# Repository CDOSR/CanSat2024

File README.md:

# CanSat2024

Welcome to the CanSat2024 project repository. This project is dedicated to the design, development, and deployment of a CanSat, a small satellite designed for educational purposes.

## Table of Contents
- [Introduction](#introduction)
- [Project Structure](#project-structure)
- [Getting Started](#getting-started)
- [Hardware](#hardware)
- [Software](#software)
- [Contributing](#contributing)
- [License](#license)

## Introduction
CanSat2024 is an educational initiative aimed at providing hands-on experience in satellite engineering. Participants will design, build, and launch a small satellite to achieve specific mission objectives.

## Project Structure
- `Documents/`: Documentation and guidelines for the project.
- `Hardware/`: Schematics, PCB designs, and hardware-related files.
- `Software/`: Source code for the CanSat's firmware and ground control software.

## Getting Started
### Prerequisites
- Basic understanding of electronics and programming.
- Required tools and components listed in `docs/tools_and_components.md`.

### Installation
1. Clone the repository:
    ```sh
    git clone https://github.com/CDOSR/CanSat2024.git
    ```
2. Navigate to the project directory:
    ```sh
    cd CanSat2024
    ```

## Hardware
Details about the hardware components, including sensors, microcontrollers, and power systems, can be found in the `hardware/` directory. Refer to `hardware/README.md` for more information.

## Software
The software for the CanSat includes firmware for onboard systems and software for ground control. Instructions for building and deploying the software are available in the `software/` directory. Refer to `software/README.md` for more details.

## Contributing
We welcome contributions from the community. Please read `CONTRIBUTING.md` for guidelines on how to contribute to the project.

## License
This project is licensed under the MIT License. See the `LICENSE` file for details.

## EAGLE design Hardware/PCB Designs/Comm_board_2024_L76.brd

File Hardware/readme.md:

# Hardware

CAD sources for the custom PCBs designed for CanSat 2024.

## Contents

- `PCB Designs/` — Eagle `.sch` (schematic) and `.brd` (board layout) files
  for the four custom boards:
  - `Comm_board_2024_L76` — communications board with Quectel L76 GNSS
  - `Comm_board_2024_M8N` — communications board with u-blox NEO-M8N GNSS
  - `Power_board_2024` — power distribution and battery management
  - `Sensor_board_2024` — sensor aggregation (IMU, environmental, etc.)

## Component datasheets

Datasheets for the third-party components used on these boards live under
[`Documentation/Hardware/Data Sheets/`](../Documentation/Hardware/Data%20Sheets/)
— kept separate so this tree stays focused on our own CAD sources rather
than vendor reference material.

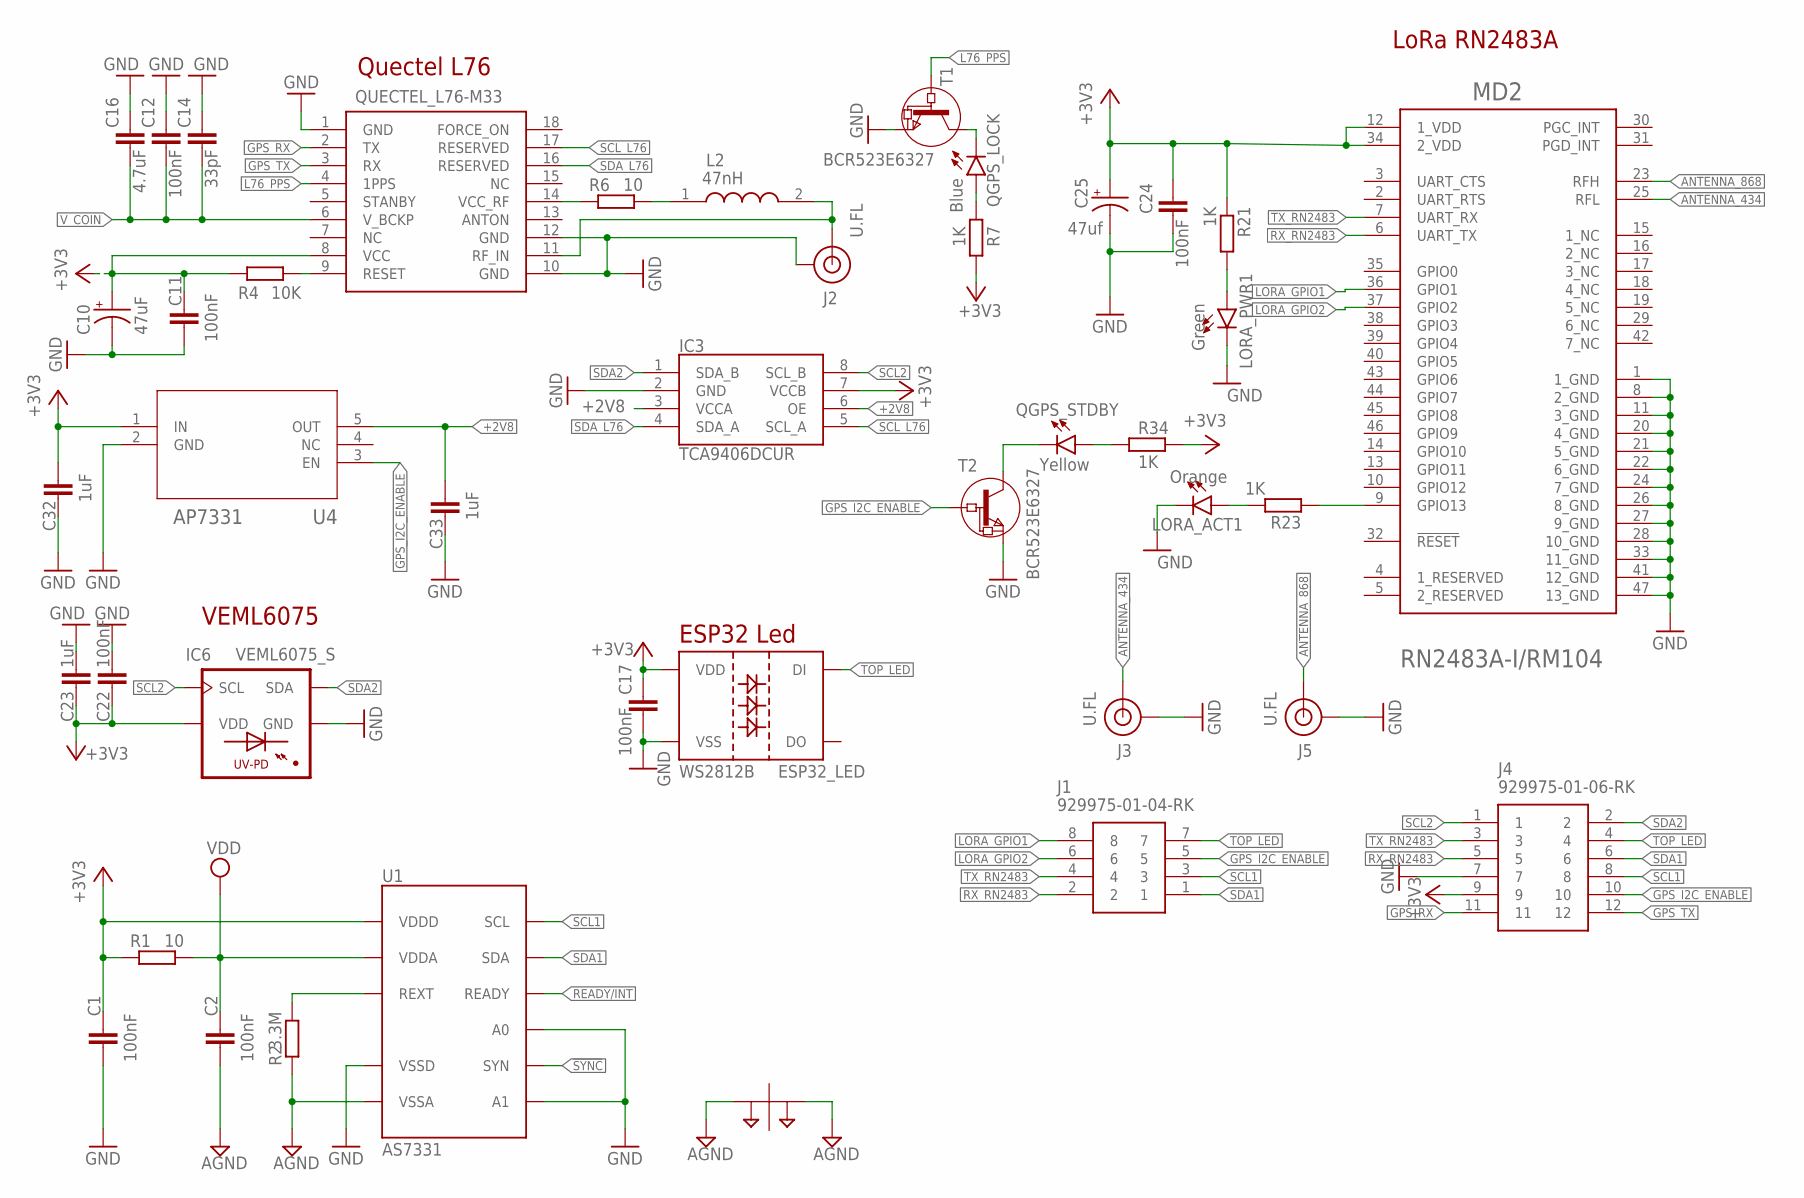
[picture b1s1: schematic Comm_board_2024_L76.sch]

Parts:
C1, C2, C11, C12, C17, C22, C24: 100nF; C0603
C10: 47uF; CAPMP6032X250N
C14: 33pF; C0603
C16: 4.7uF; C0603
C23, C32, C33: 1uF; C0603
C25: 47uf; CAPMP6032X250N
ESP32_LED: WS2812B
IC3: TCA9406DCUR; SOP50P310X90-8N
IC6: VEML6075_S; VISHAY_VEML6075_1.25X2X1
J1: 929975-01-04-RK; RHDR8W76P254_2X4_1016X508X839P
J2, J3, J5: U.FL; SPARKFUN-CONNECTORS_SPARKFUN-CONNECTORS_U.FL
J4: 929975-01-06-RK; RHDR12W76P254_2X6_1524X508X839
L2: 47nH; LQW2UAS12NG00L
LORA_ACT1: Orange; CHIP-LED0603
LORA_PWR1: Green; CHIP-LED0603
MD2: RM104_MICROCHIP_RN2483A-I-RM104MICROCHIP_RN2483A-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; RM104_MICROCHIP_RN2483A-I-RM104_0
QGPS_LOCK: Blue; CHIP-LED0603
QGPS_STDBY: Yellow; CHIP-LED0603
QUECTEL_L76-M33: L76 - M33; L76-M33
R1, R6: 10; R0603
R2: 3.3M; R0603
R4: 10K; R0603
R7, R21, R23, R34: 1K; R0603
SUPPLYTIE1: SPARKFUN-POWERSYMBOLS_2PT_GND_TIE
T1, T2: BCR523E6327; SOT-23
U1: AS7331; SPARKFUN_QWIIC_UV_SENSOR_AS7331_OLGA16
U4: AP7331; SOT25_DIO

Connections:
!SYNC: U1.8 (SYN)
+2V8: C33.2, IC3.3 (VCCA), IC3.6 (OE), U4.5 (OUT)
+3V3: C1.2, C10.1 (+), C11.2, C17.1, C22.2, C23.1, C24.1, C25.1 (+), C32.2, ESP32_LED.1 (VDD), IC3.7 (VCCB), IC6.4 (VDD), J4.9, MD2.12 (1_VDD), MD2.34 (2_VDD), QUECTEL_L76-M33.8 (VCC), R1.1, R4.1, R7.1, R21.1, R34.2, U1.10 (VDDD), U4.1 (IN)
AGND: C2.1, R2.1, SUPPLYTIE1.P$1, SUPPLYTIE1.P$2, U1.1 (VSSA), U1.2 (VSSA), U1.5 (VSSA), U1.6 (VSSA), U1.15 (VSSA), U1.16 (VSSA)
ANT1: J2.FEED (SIGNAL), L2.2, QUECTEL_L76-M33.11 (RF_IN)
ANTENNA_434: J3.FEED (SIGNAL), MD2.25 (RFL)
ANTENNA_868: J5.FEED (SIGNAL), MD2.23 (RFH)
GND: C1.1, C10.2 (-), C11.1, C12.2, C14.2, C16.2, C17.2, C22.1, C23.2, C24.2, C25.2 (-), C32.1, C33.1, ESP32_LED.3 (VSS), IC3.2 (GND), IC6.1 (GND), J2.1 (GND), J2.2 (GND), J2.3 (GND), J3.1 (GND), J3.2 (GND), J3.3 (GND), J4.7, J5.1 (GND), J5.2 (GND), J5.3 (GND), LORA_ACT1.C, LORA_PWR1.C, MD2.1 (1_GND), MD2.8 (2_GND), MD2.11 (3_GND), MD2.20 (4_GND), MD2.21 (5_GND), MD2.22 (6_GND), MD2.24 (7_GND), MD2.26 (8_GND), MD2.27 (9_GND), MD2.28 (10_GND), MD2.33 (11_GND), MD2.41 (12_GND), MD2.47 (13_GND), QUECTEL_L76-M33.1 (GND), QUECTEL_L76-M33.10 (GND), QUECTEL_L76-M33.12 (GND), T1.2 (E), T2.2 (E), U1.7 (A1), U1.11 (VSSD), U1.14 (A0), U4.2 (GND)
GPS2_RESET: QUECTEL_L76-M33.9 (RESET), R4.2
GPS_I2C_ENABLE: J1.5, J4.10, T2.3 (B), U4.3 (EN)
GPS_RX: J4.11, QUECTEL_L76-M33.2 (TX)
GPS_TX: J4.12, QUECTEL_L76-M33.3 (RX)
L76_PPS: QUECTEL_L76-M33.4 (1PPS), T1.3 (B)
LORA_GPIO1: J1.8, MD2.36 (GPIO1)
LORA_GPIO2: J1.6, MD2.37 (GPIO2)
unnamed: QGPS_LOCK.C, T1.1 (C)
unnamed: R2.2, U1.4 (REXT)
unnamed: QGPS_STDBY.C, T2.1 (C)
unnamed: L2.1, R6.2
unnamed: QGPS_STDBY.A, R34.1
unnamed: QUECTEL_L76-M33.14 (VCC_RF), R6.1
unnamed: QGPS_LOCK.A, R7.2
unnamed: MD2.9 (GPIO13), R23.1
unnamed: LORA_ACT1.A, R23.2
unnamed: LORA_PWR1.A, R21.2
READY/INT: U1.9 (READY)
RX_RN2483: J1.2, J4.5, MD2.6 (UART_TX)
SCL1: J1.3, J4.8, U1.13 (SCL)
SCL2: IC3.8 (SCL_B), IC6.3 (SCL), J4.1
SCL_L76: IC3.5 (SCL_A), QUECTEL_L76-M33.17 (RESERVED)
SDA1: J1.1, J4.6, U1.12 (SDA)
SDA2: IC3.1 (SDA_B), IC6.2 (SDA), J4.2
SDA_L76: IC3.4 (SDA_A), QUECTEL_L76-M33.16 (RESERVED)
TOP_LED: ESP32_LED.4 (DI), J1.7, J4.4
TX_RN2483: J1.4, J4.3, MD2.7 (UART_RX)
VDD: C2.2, R1.2, U1.3 (VDDA)
V_COIN: C12.1, C14.1, C16.1, QUECTEL_L76-M33.6 (V_BCKP)

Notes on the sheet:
Quectel L76
ESP32 Led
VEML6075
LoRa RN2483A

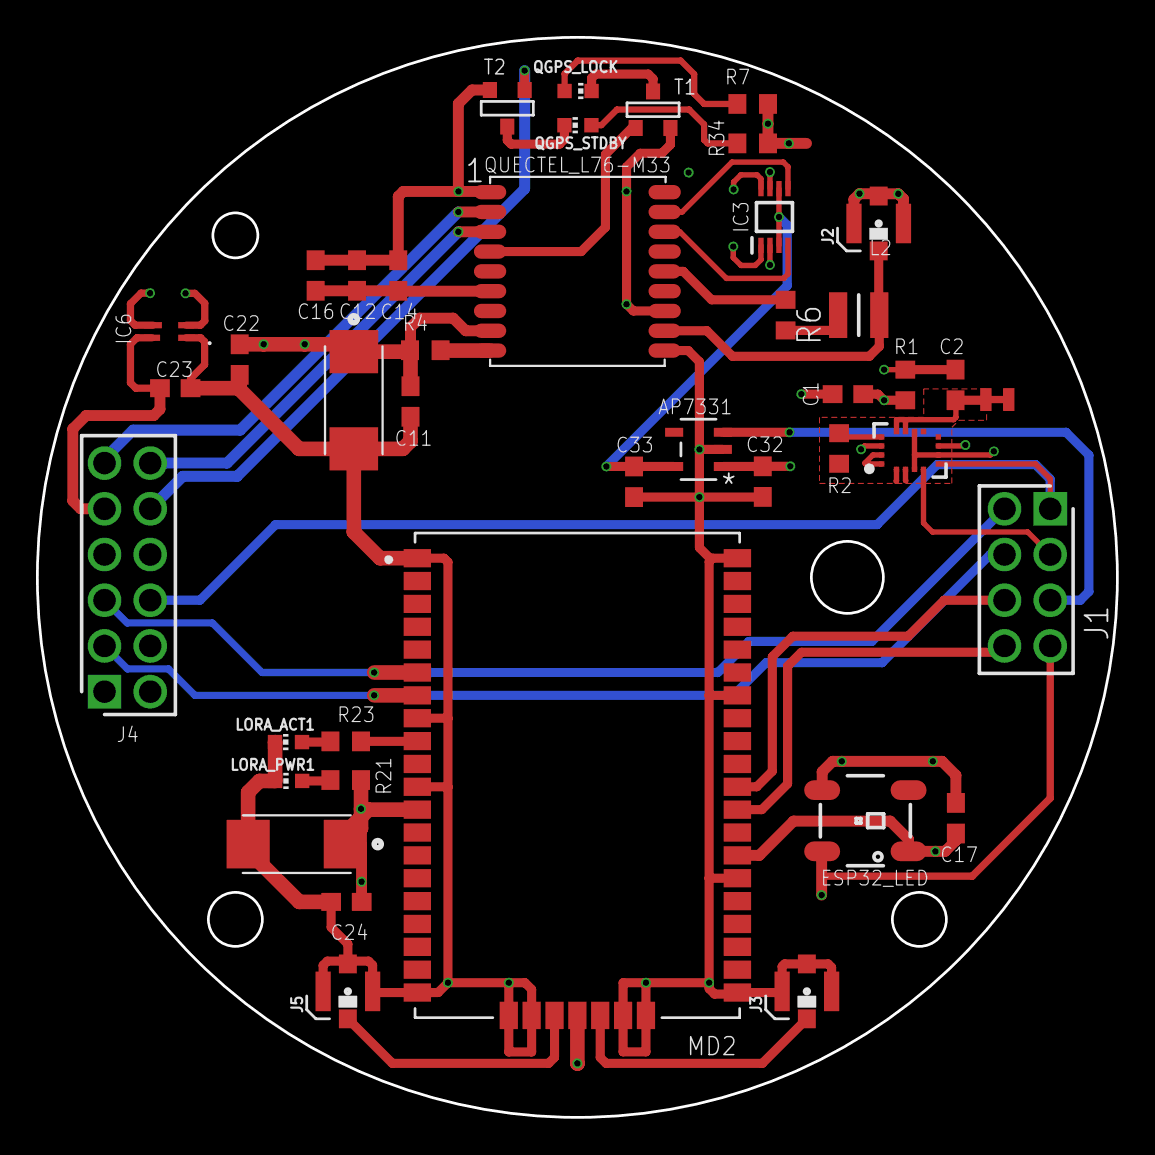
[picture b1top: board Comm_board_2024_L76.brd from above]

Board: 4 copper layers, 60.0 x 60.0 mm, 42 parts (0 on the bottom side), 35 nets.

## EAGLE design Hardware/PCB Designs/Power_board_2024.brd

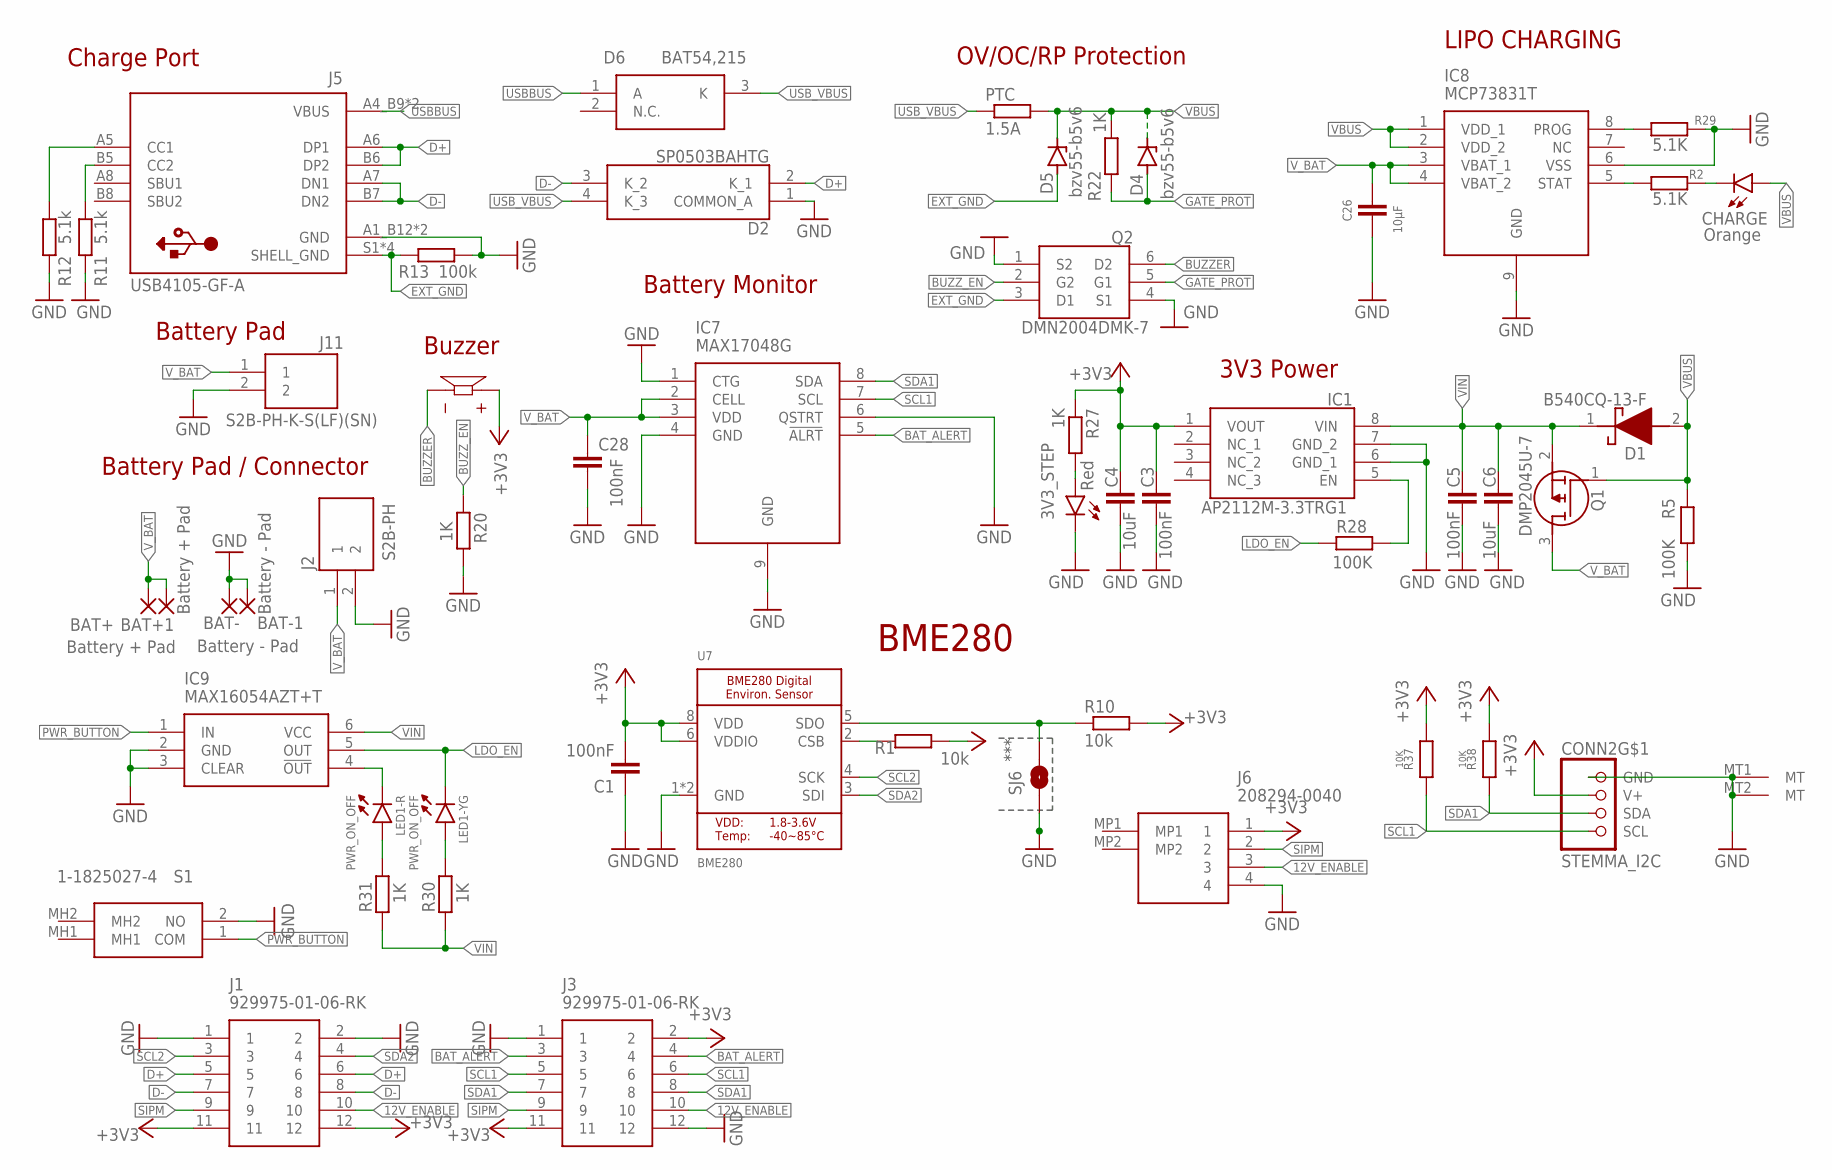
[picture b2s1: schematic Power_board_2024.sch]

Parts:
3V3_STEP: Red; CHIPLED_0805
BAT+, BAT+1: Battery + Pad; SMD2,54-5,08
BAT-, BAT-1: Battery - Pad; SMD2,54-5,08
BUZZER: CMI-1210-5-95T; XDCR_CMI-1210-5-95T
C1, C3, C5, C28: 100nF; C0603
C4, C6: 10uF; C0603
C26: 10µF; C0603
CHARGE: Orange; CHIPLED_0805
CONN2: STEMMA_I2C; JST_SH4
D1: B540CQ-13-F; DIOM7959X250N
D2: SP0503BAHTG
D4, D5: bzv55-b5v6; SOD80C
D6: BAT54,215; SOT95P230X110-3N
IC1: AP2112M-3.3TRG1; SOIC127P600X170-8N
IC7: MAX17048G; SON50P200X200X80-9N
IC8: MCP73831T; SON50P300X200X100-9N
IC9: MAX16054AZT+T; SOT95P275X110-6N
J1, J3: 929975-01-06-RK; RHDR12W76P254_2X6_1524X508X839
J2: S2B-PH; JST_S2B-PH-K-S(LF)(SN)
J5: USB4105-GF-A; GCT_USB4105-GF-A
J6: 208294-0040; 2082940040
J11: S2B-PH-K-S(LF)(SN); JST_S2B-PH-K-S(LF)(SN)
LED1: PWR_ON_OFF; 3216(1206)-4
PTC: 1.5A; R2512
Q1: DMP2045U-7; SOT96P240X110-3N
Q2: DMN2004DMK-7; SOT95P285X145-6N
R1, R10: 10k; R0603
R2, R29: 5.1K; R0603
R5, R28: 100K; R0603
R11, R12: 5.1k; R0603
R13: 100k; R0603
R20, R22, R27, R30, R31: 1K; R0603
R37, R38: 10K; R0603
S1: 1-1825027-4; 118250274
SJ6: SOLDER_JUMPER; SPARKFUN_SJ_2S-NO
U7: BME280

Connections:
12V_ENABLE: J1.10, J3.10, J6.3
+3V3: BUZZER.P, C1.2, C3.2, C4.2, CONN2.2 (V+), IC1.1 (VOUT), J1.11, J1.12, J3.2, J3.11, J6.1, R1.1, R10.2, R27.1, R37.2, R38.2, U7.6 (VDDIO), U7.8 (VDD)
BAT_ALERT: IC7.5 (!ALRT), J3.3, J3.4
BUZZER: BUZZER.N, Q2.6 (D2)
BUZZ_EN: Q2.2 (G2), R20.1
D+: D2.2 (K_1), J1.5, J1.6, J5.A6 (DP1), J5.B6 (DP2)
D-: D2.3 (K_2), J1.7, J1.8, J5.A7 (DN1), J5.B7 (DN2)
EXT_GND: D5.A, J5.S1 (SHELL_GND), J5.S2 (SHELL_GND), J5.S3 (SHELL_GND), J5.S4 (SHELL_GND), Q2.3 (D1), R13.2
FSYNC2: R10.1, SJ6.2, U7.5 (SDO)
GATE_PROT: D4.A, Q2.5 (G1), R22.1
GND: 3V3_STEP.C, BAT-.1, BAT-1.1, C1.1, C3.1, C4.1, C5.1, C6.1, C26.2, C28.2, CONN2.1 (GND), CONN2.MT1 (MT), CONN2.MT2 (MT), D2.1 (COMMON_A), IC1.6 (GND_1), IC1.7 (GND_2), IC7.1 (CTG), IC7.4 (GND), IC7.6 (QSTRT), IC7.9 (GND), IC8.6 (VSS), IC8.9 (GND), IC9.2 (GND), IC9.3 (CLEAR), J1.1, J1.2, J2.2, J3.1, J3.12, J5.A1_B12 (GND), J5.B1_A12 (GND), J6.4, J11.2, Q2.1 (S2), Q2.4 (S1), R5.2, R11.1, R12.1, R13.1, R20.2, R29.1, S1.2 (NO), SJ6.1, U7.1 (GND), U7.7 (GND)
LDO_EN: IC9.5 (OUT), LED1.3 (C), R28.1
unnamed: R1.2, U7.2 (CSB)
unnamed: IC8.5 (STAT), R2.2
unnamed: CHARGE.C, R2.1
unnamed: IC8.8 (PROG), R29.2
unnamed: IC9.4 (!OUT), LED1.1 (C)
unnamed: IC1.5 (EN), R28.2
unnamed: LED1.4 (A), R30.2
unnamed: LED1.2 (A), R31.2
unnamed: J5.B5 (CC2), R11.2
unnamed: J5.A5 (CC1), R12.2
unnamed: 3V3_STEP.A, R27.2
PWR_BUTTON: IC9.1 (IN), S1.1 (COM)
SCL1: CONN2.4 (SCL), IC7.7 (SCL), J3.5, J3.6, R37.1
SCL2: J1.3, U7.4 (SCK)
SDA1: CONN2.3 (SDA), IC7.8 (SDA), J3.7, J3.8, R38.1
SDA2: J1.4, U7.3 (SDI)
SIPM: J1.9, J3.9, J6.2
USBBUS: D6.1 (A), J5.A4_B9 (VBUS), J5.B4_A9 (VBUS)
USB_VBUS: D2.4 (K_3), D6.3 (K), PTC.1
VBUS: CHARGE.A, D1.2 (A), D4.C, D5.C, IC8.1 (VDD_1), IC8.2 (VDD_2), PTC.2, Q1.1 (G), R5.1, R22.2
VIN: C5.2, C6.2, D1.1 (K), IC1.8 (VIN), IC9.6 (VCC), Q1.2 (S), R30.1, R31.1
V_BAT: BAT+.1, BAT+1.1, C26.1, C28.1, IC7.2 (CELL), IC7.3 (VDD), IC8.3 (VBAT_1), IC8.4 (VBAT_2), J2.1, J11.1, Q1.3 (D)

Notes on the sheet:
Battery Pad
3V3 Power
Charge Port
Battery Pad / Connector
Buzzer
OV/OC/RP Protection
Battery Monitor
LIPO CHARGING
BME280
***

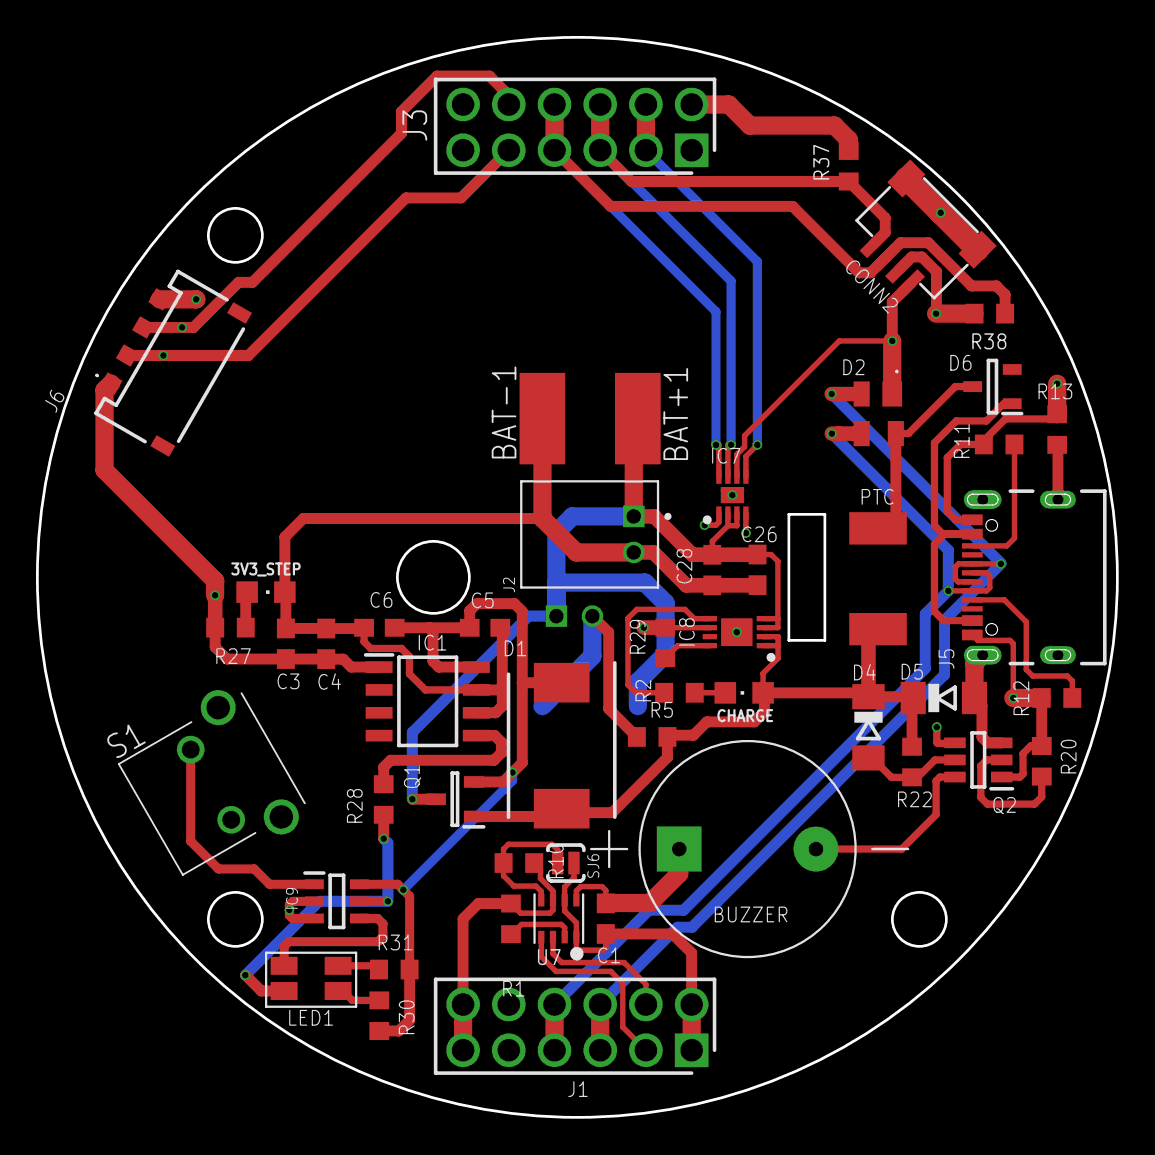
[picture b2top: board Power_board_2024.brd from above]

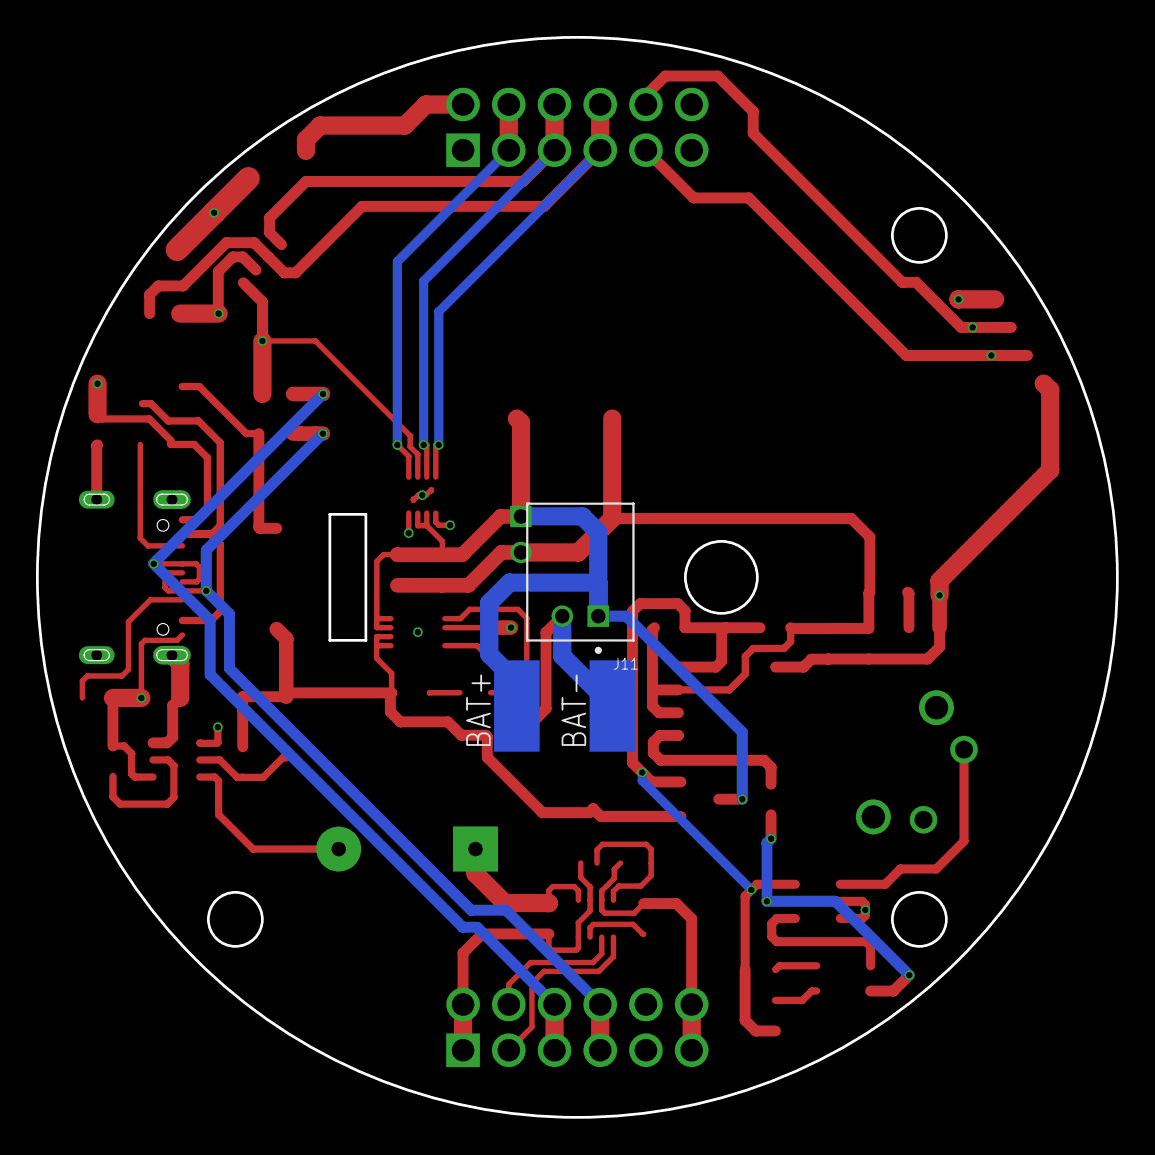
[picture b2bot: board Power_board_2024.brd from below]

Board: 4 copper layers, 60.0 x 60.0 mm, 53 parts (3 on the bottom side), 34 nets.

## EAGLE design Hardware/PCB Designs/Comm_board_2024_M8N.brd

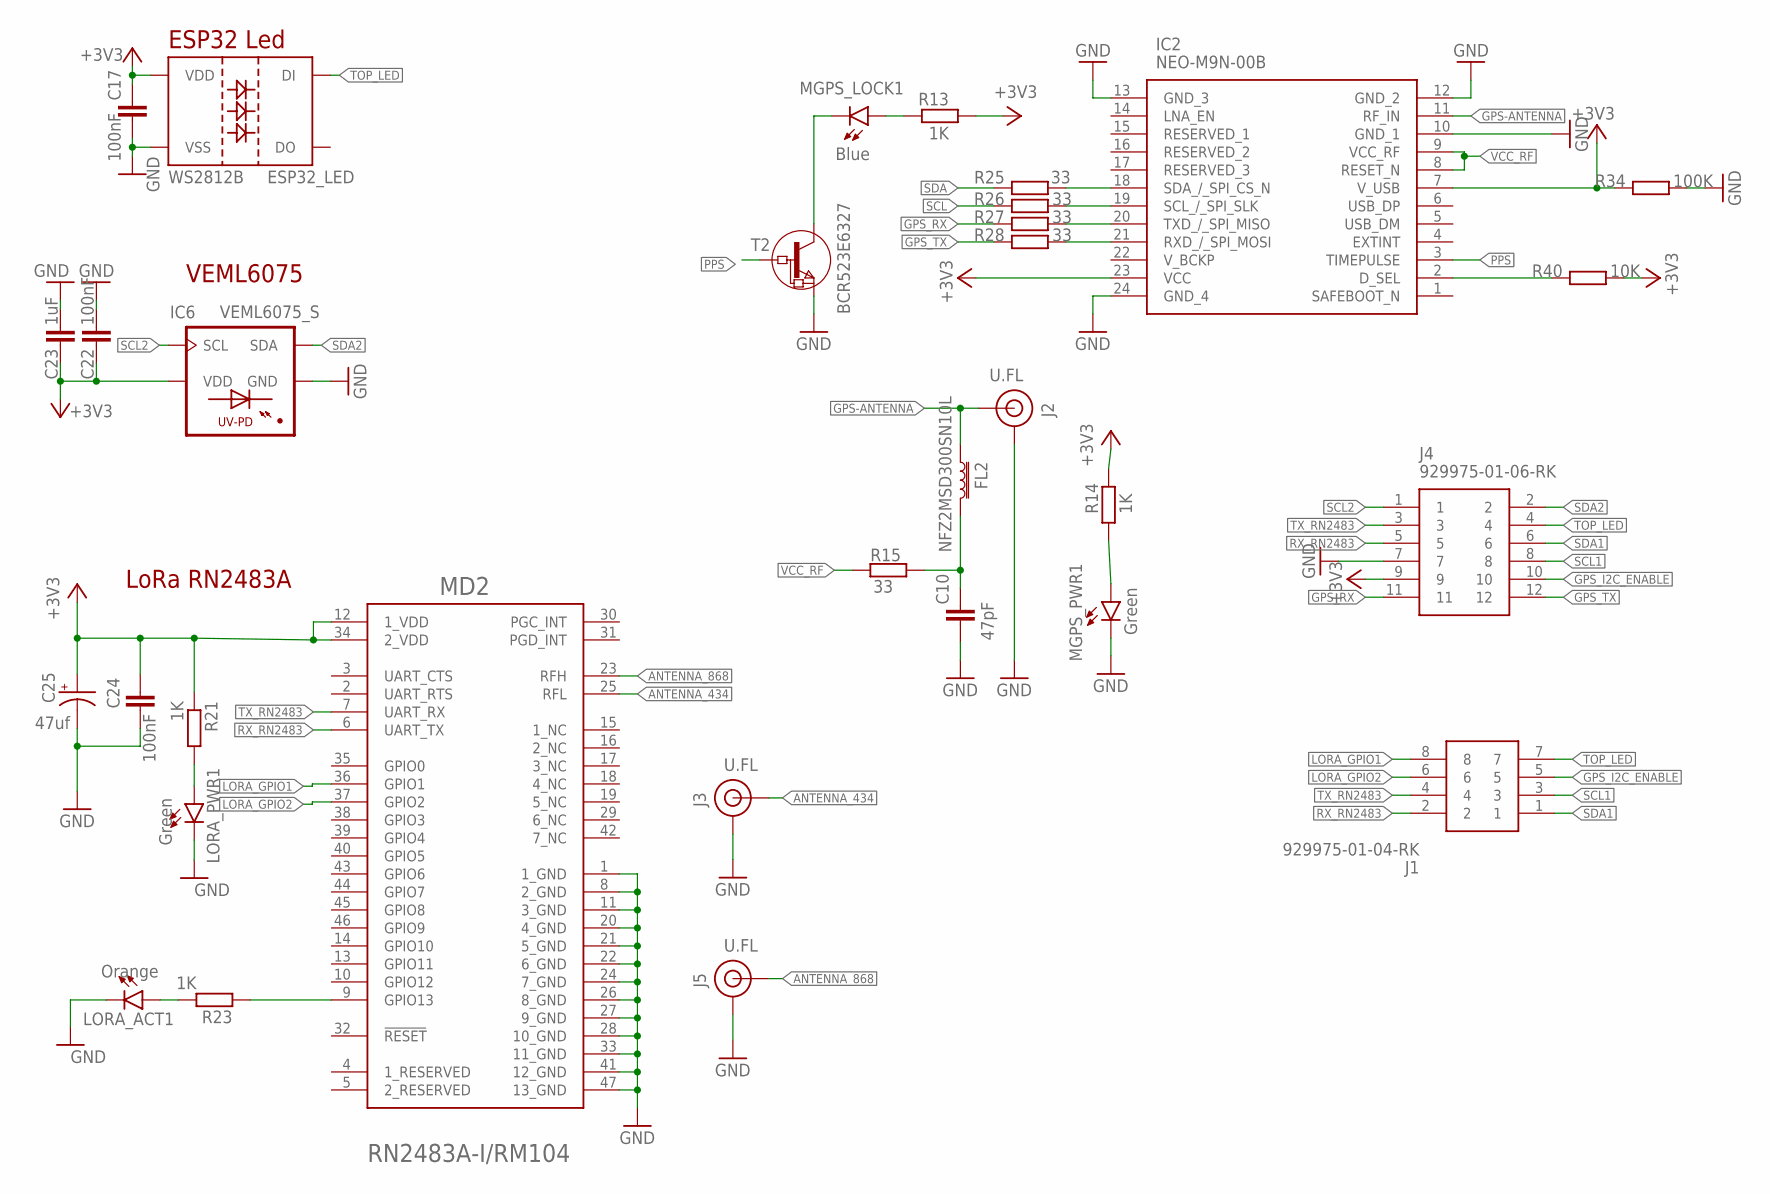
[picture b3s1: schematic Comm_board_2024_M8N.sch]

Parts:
C10: 47pF; C0603
C17, C22, C24: 100nF; C0603
C23: 1uF; C0603
C25: 47uf; CAPMP6032X250N
ESP32_LED: WS2812B
FL2: NFZ2MSD300SN10L; BEADC2016X120N
IC2: NEO-M9N-00B; NEOM9N00B
IC6: VEML6075_S; VISHAY_VEML6075_1.25X2X1
J1: 929975-01-04-RK; RHDR8W76P254_2X4_1016X508X839P
J2, J3, J5: U.FL; SPARKFUN-CONNECTORS_SPARKFUN-CONNECTORS_U.FL
J4: 929975-01-06-RK; RHDR12W76P254_2X6_1524X508X839
LORA_ACT1: Orange; CHIP-LED0603
LORA_PWR1: Green; CHIP-LED0603
MD2: RM104_MICROCHIP_RN2483A-I-RM104MICROCHIP_RN2483A-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; RM104_MICROCHIP_RN2483A-I-RM104_0
MGPS_LOCK1: Blue; CHIP-LED0603
MGPS_PWR1: Green; CHIP-LED0603
R13, R14, R21, R23: 1K; R0603
R15, R25, R26, R27, R28: 33; R0603
R34: 100K; R0603
R40: 10K; R0603
T2: BCR523E6327; SOT-23

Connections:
+3V3: C17.1, C22.2, C23.1, C24.1, C25.1 (+), ESP32_LED.1 (VDD), IC2.7 (V_USB), IC2.23 (VCC), IC6.4 (VDD), J4.9, MD2.12 (1_VDD), MD2.34 (2_VDD), R13.1, R14.2, R21.1, R34.2, R40.1
ANTENNA_434: J3.FEED (SIGNAL), MD2.25 (RFL)
ANTENNA_868: J5.FEED (SIGNAL), MD2.23 (RFH)
GND: C10.2, C17.2, C22.1, C23.2, C24.2, C25.2 (-), ESP32_LED.3 (VSS), IC2.10 (GND_1), IC2.12 (GND_2), IC2.13 (GND_3), IC2.24 (GND_4), IC6.1 (GND), J2.1 (GND), J2.2 (GND), J2.3 (GND), J3.1 (GND), J3.2 (GND), J3.3 (GND), J4.7, J5.1 (GND), J5.2 (GND), J5.3 (GND), LORA_ACT1.C, LORA_PWR1.C, MD2.1 (1_GND), MD2.8 (2_GND), MD2.11 (3_GND), MD2.20 (4_GND), MD2.21 (5_GND), MD2.22 (6_GND), MD2.24 (7_GND), MD2.26 (8_GND), MD2.27 (9_GND), MD2.28 (10_GND), MD2.33 (11_GND), MD2.41 (12_GND), MD2.47 (13_GND), MGPS_PWR1.C, R34.1, T2.2 (E)
GPS-ANTENNA: FL2.1 (3), IC2.11 (RF_IN), J2.FEED (SIGNAL)
GPS_I2C_ENABLE: J1.5, J4.10
GPS_RX: J4.11, R27.2
GPS_TX: J4.12, R28.2
LORA_GPIO1: J1.8, MD2.36 (GPIO1)
LORA_GPIO2: J1.6, MD2.37 (GPIO2)
unnamed: MGPS_LOCK1.A, R13.2
unnamed: MGPS_PWR1.A, R14.1
unnamed: IC2.20 (TXD_/_SPI_MISO), R27.1
unnamed: IC2.19 (SCL_/_SPI_SLK), R26.1
unnamed: IC2.18 (SDA_/_SPI_CS_N), R25.1
unnamed: IC2.21 (RXD_/_SPI_MOSI), R28.1
unnamed: IC2.2 (D_SEL), R40.2
unnamed: MGPS_LOCK1.C, T2.1 (C)
unnamed: C10.1, FL2.2 (4), R15.1
unnamed: MD2.9 (GPIO13), R23.1
unnamed: LORA_ACT1.A, R23.2
unnamed: LORA_PWR1.A, R21.2
PPS: IC2.3 (TIMEPULSE), T2.3 (B)
RX_RN2483: J1.2, J4.5, MD2.6 (UART_TX)
SCL: R26.2
SCL1: J1.3, J4.8
SCL2: IC6.3 (SCL), J4.1
SDA: R25.2
SDA1: J1.1, J4.6
SDA2: IC6.2 (SDA), J4.2
TOP_LED: ESP32_LED.4 (DI), J1.7, J4.4
TX_RN2483: J1.4, J4.3, MD2.7 (UART_RX)
VCC_RF: IC2.8 (RESET_N), IC2.9 (VCC_RF), R15.2

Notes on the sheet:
ESP32 Led
VEML6075
LoRa RN2483A

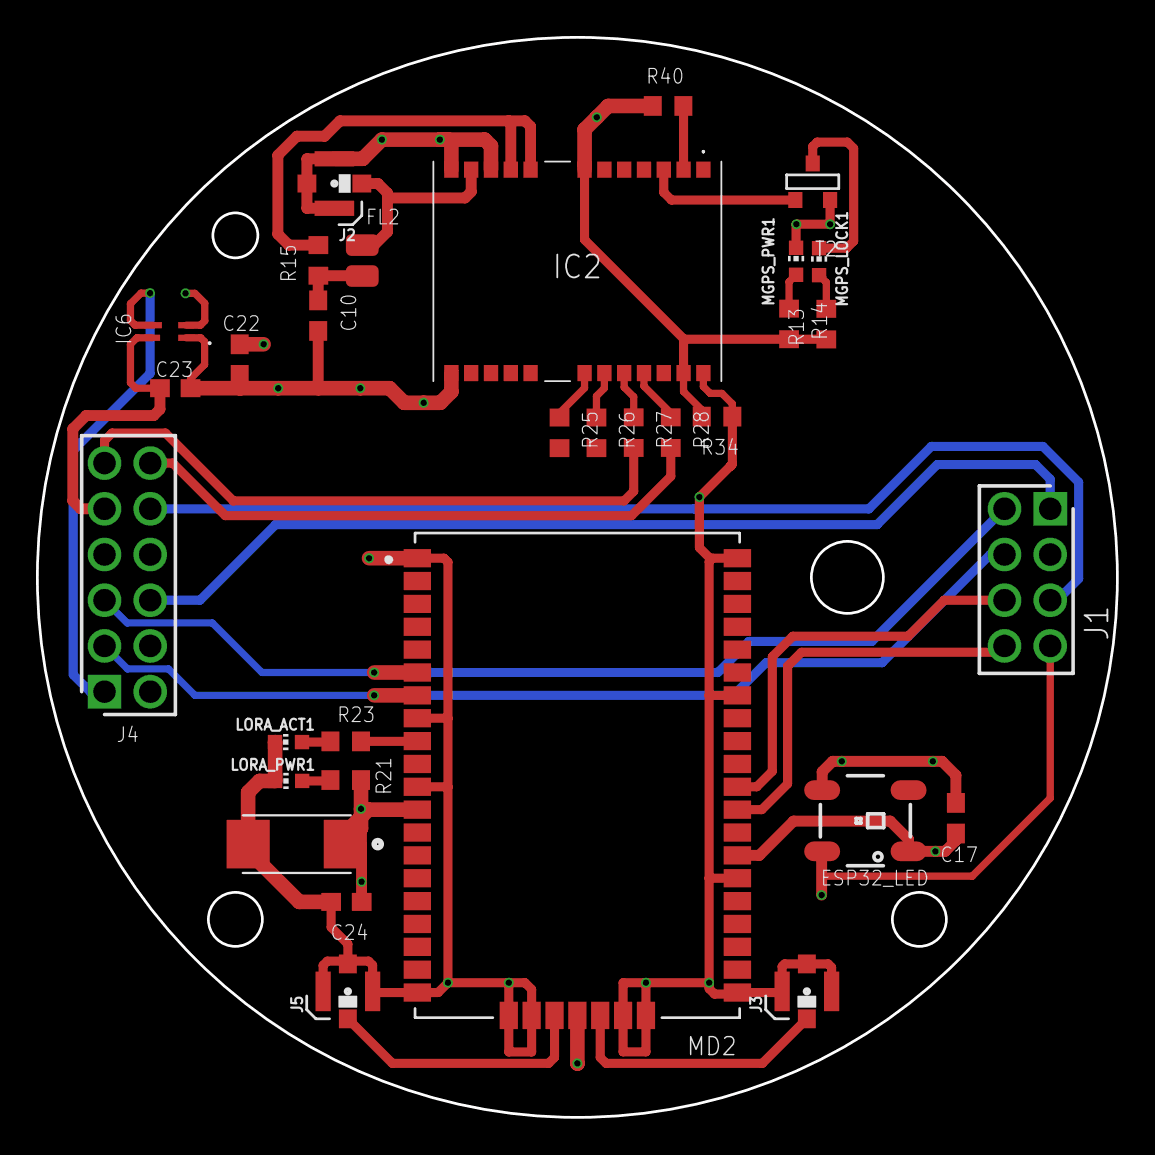
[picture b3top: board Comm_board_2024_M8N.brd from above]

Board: 4 copper layers, 60.0 x 60.0 mm, 32 parts (0 on the bottom side), 31 nets.

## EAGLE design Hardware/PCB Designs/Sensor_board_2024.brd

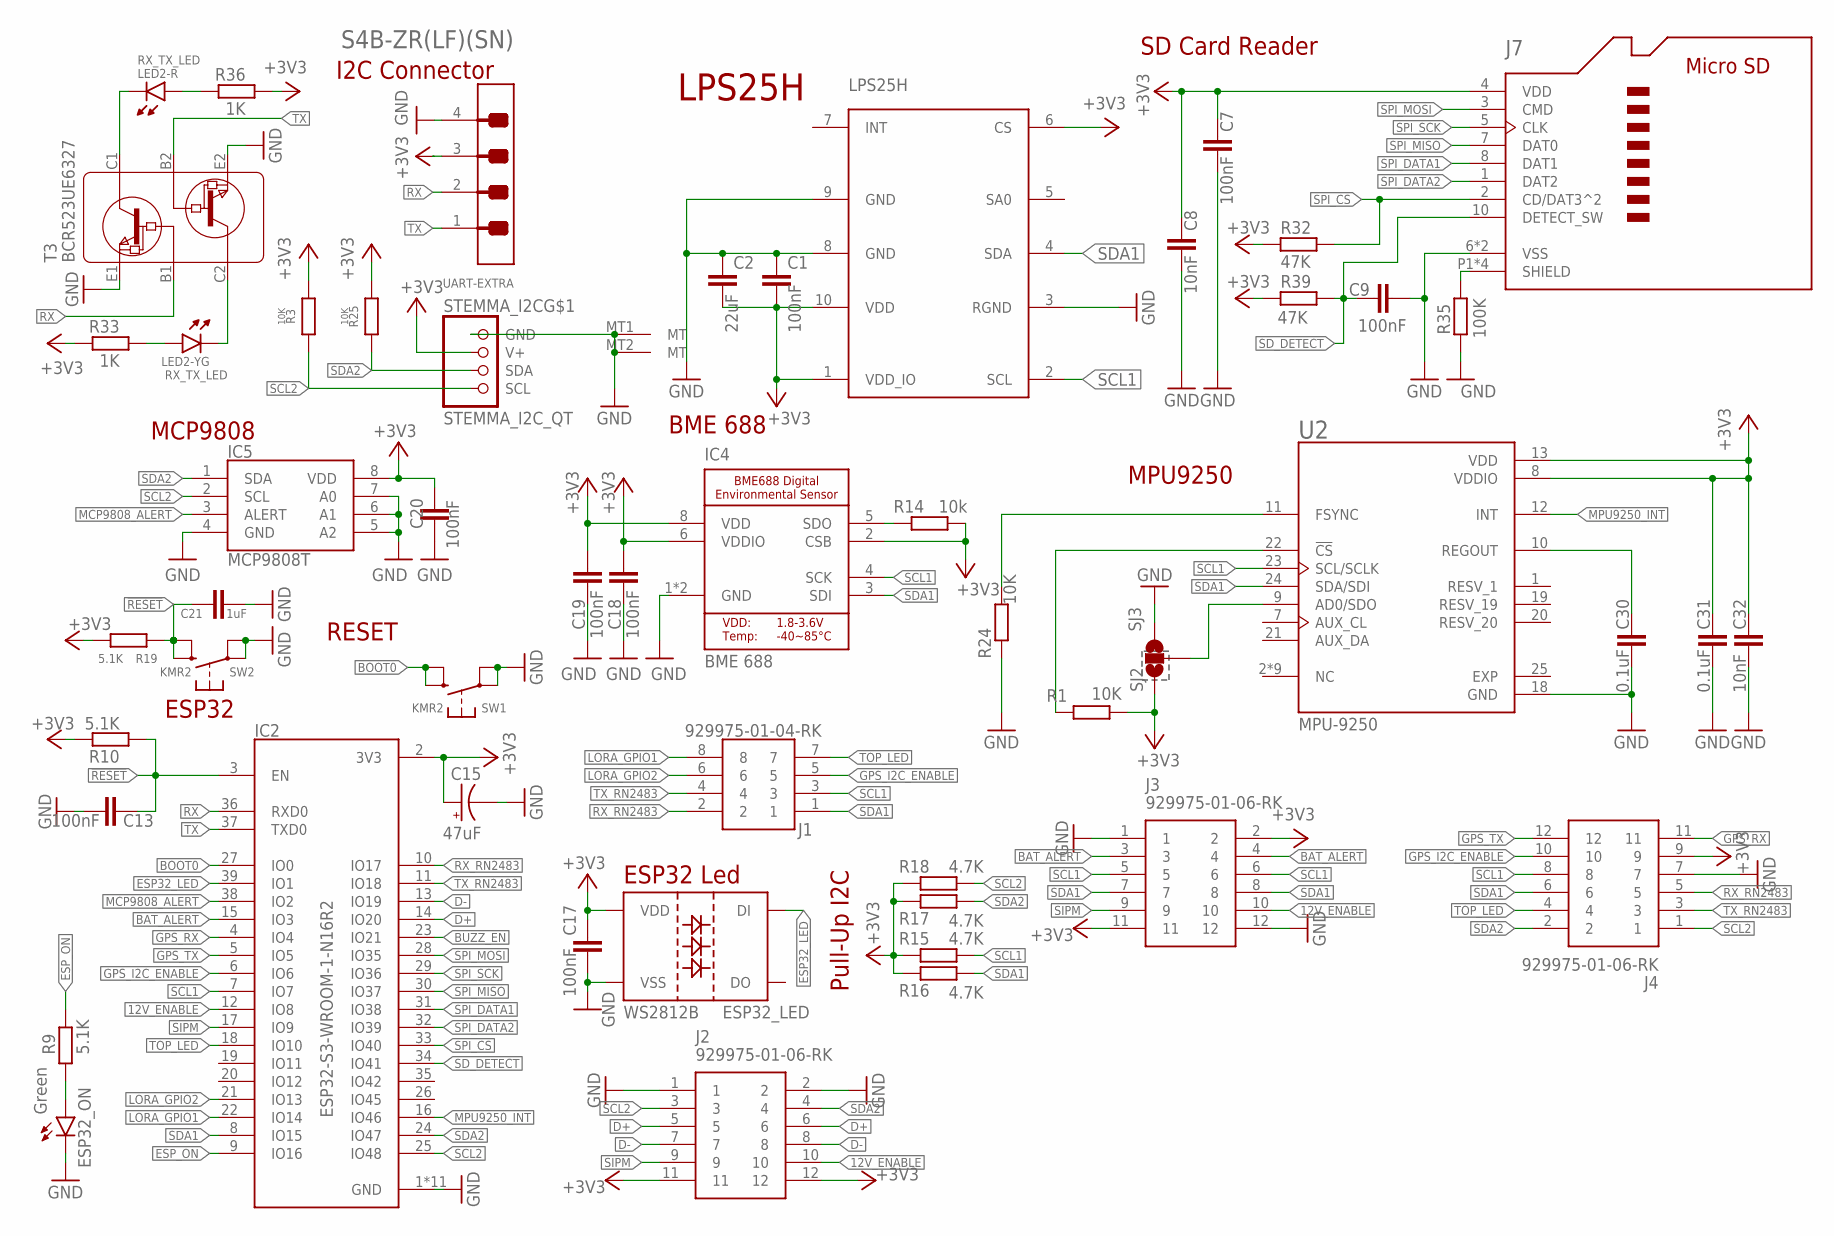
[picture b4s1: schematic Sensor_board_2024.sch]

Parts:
C1, C7, C9, C13, C17, C18, C19, C20: 100nF; C0603
C2: 22uF; C0603
C8: 10nF; C0603
C15: 47uF; CAPMP6032X250N
C21: 1uF; C0603
C30, C31: 0.1uF; 0603-CAP
C32: 10nF; 0603-CAP
ESP32_LED: WS2812B
ESP32_ON: Green; CHIPLED_0805
IC2: ESP32-S3-WROOM-1-N16R2; XCVR_ESP32-S3-WROOM-1-N16R2
IC4: BME 688; BME_688
IC5: MCP9808T; SOP65P490X110-8N
J1: 929975-01-04-RK; RHDR8W76P254_2X4_1016X508X839P
J2, J3, J4: 929975-01-06-RK; RHDR12W76P254_2X6_1524X508X839
J7: 503398-1892; MOLEX_503398-1892
LED2: RX_TX_LED; 3216(1206)-4
LPS25H: LPS25H
R1, R3, R24, R25: 10K; R0603
R9, R10, R19: 5.1K; R0603
R14: 10k; R0603
R15, R16, R17, R18: 4.7K; R0603
R32, R39: 47K; R0603
R33, R36: 1K; R0603
R35: 100K; R0603
SJ2: SJ3; SPARKFUN_SJ_3
STEMMA_I2C: STEMMA_I2C_QT; JST_SH4
SW1, SW2: KMR2; BTN_KMR2_4.6X2.8
T3: BCR523UE6327; SOT-23
U2: MPU-9250; QFN40P300X300X105-25N
UART-EXTRA: JST_S4B-ZR_LF; JST_S4B-ZR_LF_SN_0

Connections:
12V_ENABLE: IC2.12 (IO8), J2.10, J3.10
!RESET: C13.1, C21.1, IC2.3 (EN), R10.1, R19.1, SW2.B (S), SW2.B' (S1)
+3V3: C1.2, C2.2, C7.1, C8.1, C15.1 (+), C17.1, C18.2, C19.2, C20.2, C31.1, C32.1, ESP32_LED.1 (VDD), IC2.2 (3V3), IC4.2 (CSB), IC4.6 (VDDIO), IC4.8 (VDD), IC5.8 (VDD), J2.11, J2.12, J3.2, J3.11, J4.9, J7.4 (VDD), LPS25H.1 (VDD_IO), LPS25H.6 (CS), LPS25H.10 (VDD), R1.2, R3.2, R10.2, R14.2, R15.2, R16.2, R17.2, R18.2, R19.2, R25.2, R32.2, R33.2, R36.1, R39.2, SJ2.1, STEMMA_I2C.2 (V+), U2.8 (VDDIO), U2.13 (VDD), UART-EXTRA.3
BAT_ALERT: IC2.15 (IO3), J3.3, J3.4
BOOT0: IC2.27 (IO0), SW1.B (S), SW1.B' (S1)
BUZZ_EN: IC2.23 (IO21)
D+: IC2.14 (IO20), J2.5, J2.6
D-: IC2.13 (IO19), J2.7, J2.8
ESP32_LED: ESP32_LED.4 (DI), IC2.39 (IO1)
ESP_ON: IC2.9 (IO16), R9.2
GND: C1.1, C2.1, C7.2, C8.2, C9.2, C13.2, C15.2 (-), C17.2, C18.1, C19.1, C20.1, C21.2, C30.2, C31.2, C32.2, ESP32_LED.3 (VSS), ESP32_ON.C, IC2.1 (GND), IC2.40 (GND), IC2.41_1 (GND), IC2.41_2 (GND), IC2.41_3 (GND), IC2.41_4 (GND), IC2.41_5 (GND), IC2.41_6 (GND), IC2.41_7 (GND), IC2.41_8 (GND), IC2.41_9 (GND), IC4.1 (GND), IC4.7 (GND), IC5.4 (GND), IC5.5 (A2), IC5.6 (A1), IC5.7 (A0), J2.1, J2.2, J3.1, J3.12, J4.7, J7.6 (VSS), J7.9 (VSS), LPS25H.3 (RGND), LPS25H.8 (GND), LPS25H.9 (GND), R24.1, R35.1, SJ2.3, STEMMA_I2C.1 (GND), STEMMA_I2C.MT1 (MT), STEMMA_I2C.MT2 (MT), SW1.A, SW1.A' (P1), SW2.A, SW2.A' (P1), T3.E1, T3.E2, U2.18 (GND), UART-EXTRA.4
GPS_I2C_ENABLE: IC2.6 (IO6), J1.5, J4.10
GPS_RX: IC2.4 (IO4), J4.11
GPS_TX: IC2.5 (IO5), J4.12
LORA_GPIO1: IC2.22 (IO14), J1.8
LORA_GPIO2: IC2.21 (IO13), J1.6
MCP9808_ALERT: IC2.38 (IO2), IC5.3 (ALERT)
MICROSD_SH2: J7.P1 (SHIELD), J7.P2 (SHIELD), J7.P3 (SHIELD), J7.P4 (SHIELD), R35.2
MPU9250_INT: IC2.16 (IO46), U2.12 (INT)
unnamed: IC4.5 (SDO), R14.1
unnamed: R1.1, U2.22 (!CS)
unnamed: R24.2, U2.11 (FSYNC)
unnamed: ESP32_ON.A, R9.1
unnamed: SJ2.2, U2.9 (AD0/SDO)
unnamed: LED2.3 (C), T3.C2
unnamed: LED2.1 (C), T3.C1
unnamed: LED2.2 (A), R36.2
unnamed: LED2.4 (A), R33.1
REGOUT: C30.1, U2.10 (REGOUT)
RESV_1: U2.1 (RESV_1)
RESV_20: U2.20 (RESV_20)
RX: IC2.36 (RXD0), T3.B1, UART-EXTRA.2
RX_RN2483: IC2.10 (IO17), J1.2, J4.5
SCL1: IC2.7 (IO7), IC4.4 (SCK), J1.3, J3.5, J3.6, J4.8, LPS25H.2 (SCL), R15.1, U2.23 (SCL/SCLK)
SCL2: IC2.25 (IO48), IC5.2 (SCL), J2.3, J4.1, R3.1, R18.1, STEMMA_I2C.4 (SCL)
SDA1: IC2.8 (IO15), IC4.3 (SDI), J1.1, J3.7, J3.8, J4.6, LPS25H.4 (SDA), R16.1, U2.24 (SDA/SDI)
SDA2: IC2.24 (IO47), IC5.1 (SDA), J2.4, J4.2, R17.1, R25.1, STEMMA_I2C.3 (SDA)
SD_DETECT: C9.1, IC2.34 (IO41), J7.10 (DETECT_SW), R39.1
SIPM: IC2.17 (IO9), J2.9, J3.9
SPI_CS: IC2.33 (IO40), J7.2 (CD/DAT3^2), R32.1
SPI_DATA1: IC2.31 (IO38), J7.8 (DAT1)
SPI_DATA2: IC2.32 (IO39), J7.1 (DAT2)
SPI_MISO: IC2.30 (IO37), J7.7 (DAT0)
SPI_MOSI: IC2.28 (IO35), J7.3 (CMD)
SPI_SCK: IC2.29 (IO36), J7.5 (CLK)
TOP_LED: IC2.18 (IO10), J1.7, J4.4
TX: IC2.37 (TXD0), T3.B2, UART-EXTRA.1
TX_RN2483: IC2.11 (IO18), J1.4, J4.3

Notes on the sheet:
ESP32
SD Card Reader
ESP32 Led
BME 688
MCP9808
Pull-Up I2C
RESET
LPS25H
MPU9250
I2C Connector

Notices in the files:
parts and their libraries:
COPYRIGHT: Copyright (C) 2022 Ultra Librarian. All rights reserved.
SparkFun-Aesthetics: Licensing: Creative Commons ShareAlike 4.0 International - https://creativecommons.org/licenses/by-sa/4.0
